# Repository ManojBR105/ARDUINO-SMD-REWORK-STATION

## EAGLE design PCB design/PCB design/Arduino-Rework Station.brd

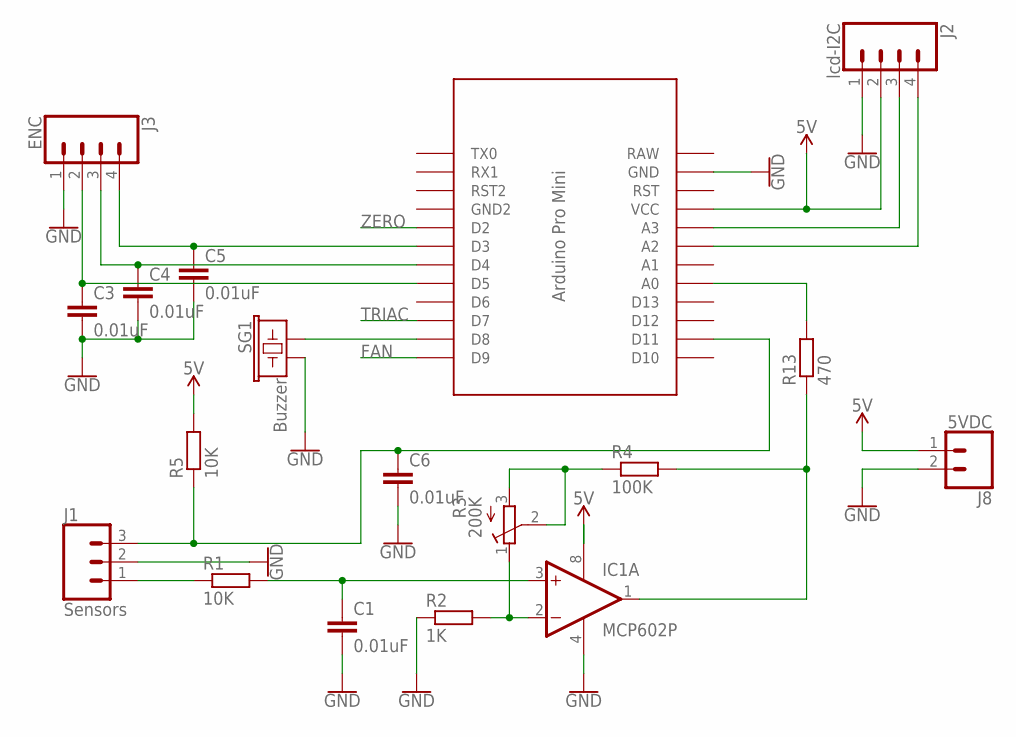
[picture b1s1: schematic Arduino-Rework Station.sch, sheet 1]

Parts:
C1, C3, C4, C5, C6: 0.01uF; C025-024X044
IC1: MCP602P; DIL08
J1: Sensors; MOLEX-1X3
J2: lcd-I2C; MOLEX-1X4
J3: ENC; MOLEX-1X4
J8: 5VDC; MOLEX-1X2
R1, R5: 10K; 0207/10
R2: 1K; 0207/10
R3: 200K; RTRIM3006P
R4: 100K; 0207/10
R13: 470; 0207/10
SG1: Buzzer; BUZZER-12MM
U$1: PRO-MINI

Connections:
5V: IC1.8 (V+), J2.2, J8.1, R5.2, U$1.VCC; also elsewhere on the board
FAN: U$1.D9; also elsewhere on the board
GND: C1.2, C3.2, C4.2, C5.2, C6.2, IC1.4 (V-), J1.2, J2.1, J3.1, J8.2, R2.1, SG1.- (2), U$1.GND; also elsewhere on the board
unnamed: C5.1, J3.4, U$1.D3
unnamed: C4.1, J3.3, U$1.D4
unnamed: C3.1, J3.2, U$1.D5
unnamed: J2.3, U$1.A3
unnamed: J2.4, U$1.A2
unnamed: J1.1, R1.1
unnamed: C1.1, IC1.3 (+IN), R1.2
unnamed: IC1.2 (-IN), R2.2, R3.1 (E)
unnamed: R3.2 (S), R3.3 (A), R4.1
unnamed: IC1.1 (OUT), R4.2, R13.1
unnamed: C6.1, J1.3, R5.1, U$1.D11
unnamed: SG1.+ (1), U$1.D8
unnamed: R13.2, U$1.A0
RAW: U$1.RAW
TRIAC: U$1.D7; also elsewhere on the board
ZERO: U$1.D2; also elsewhere on the board

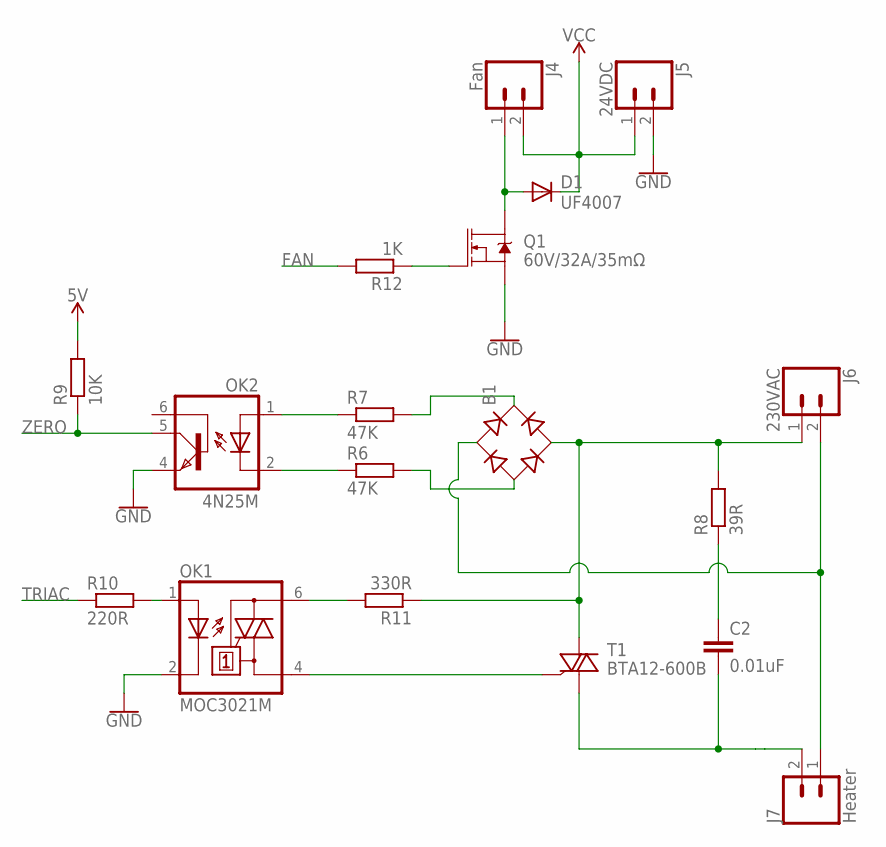
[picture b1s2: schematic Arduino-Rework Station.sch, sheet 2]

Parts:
B1: RB1A
C2: 0.01uF; C050-045X075
D1: UF4007; DO41-10
J4: Fan; MOLEX-1X2
J5: 24VDC; SCREWTERMINAL-5MM-2
J6: 230VAC; 1X02_XTRA_BIG
J7: Heater; 1X02_XTRA_BIG
OK1: MOC3021M; DIL06
OK2: 4N25M; DIL06
Q1: 60V/32A/35mΩ; TO220V
R6, R7: 47K; 0204/7
R8: 39R; 0617/22
R9: 10K; 0204/7
R10: 220R; 0204/7
R11: 330R; 0204/7
R12: 1K; 0204/7
T1: BTA12-600B; TO220BV

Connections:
5V: R9.2; also elsewhere on the board
FAN: R12.2; also elsewhere on the board
GND: J5.2, OK1.2 (C), OK2.4 (EMI), Q1.3 (S); also elsewhere on the board
unnamed: OK1.1 (A), R10.2
unnamed: OK2.1 (A), R7.1
unnamed: OK2.2 (C), R6.1
unnamed: B1.+, R7.2
unnamed: B1.-, R6.2
unnamed: B1.AC2, J6.1, R8.2, R11.1, T1.T2 (A2)
unnamed: C2.1, R8.1
unnamed: B1.AC1, J6.2, J7.1
unnamed: OK1.6 (A2), R11.2
unnamed: OK1.4 (A1), T1.G
unnamed: D1.A, J4.1, Q1.2 (D)
unnamed: C2.2, J7.2, T1.T1 (A1)
unnamed: Q1.1 (G), R12.1
TRIAC: R10.1; also elsewhere on the board
VCC: D1.C, J4.2, J5.1
ZERO: OK2.5 (COL), R9.1; also elsewhere on the board

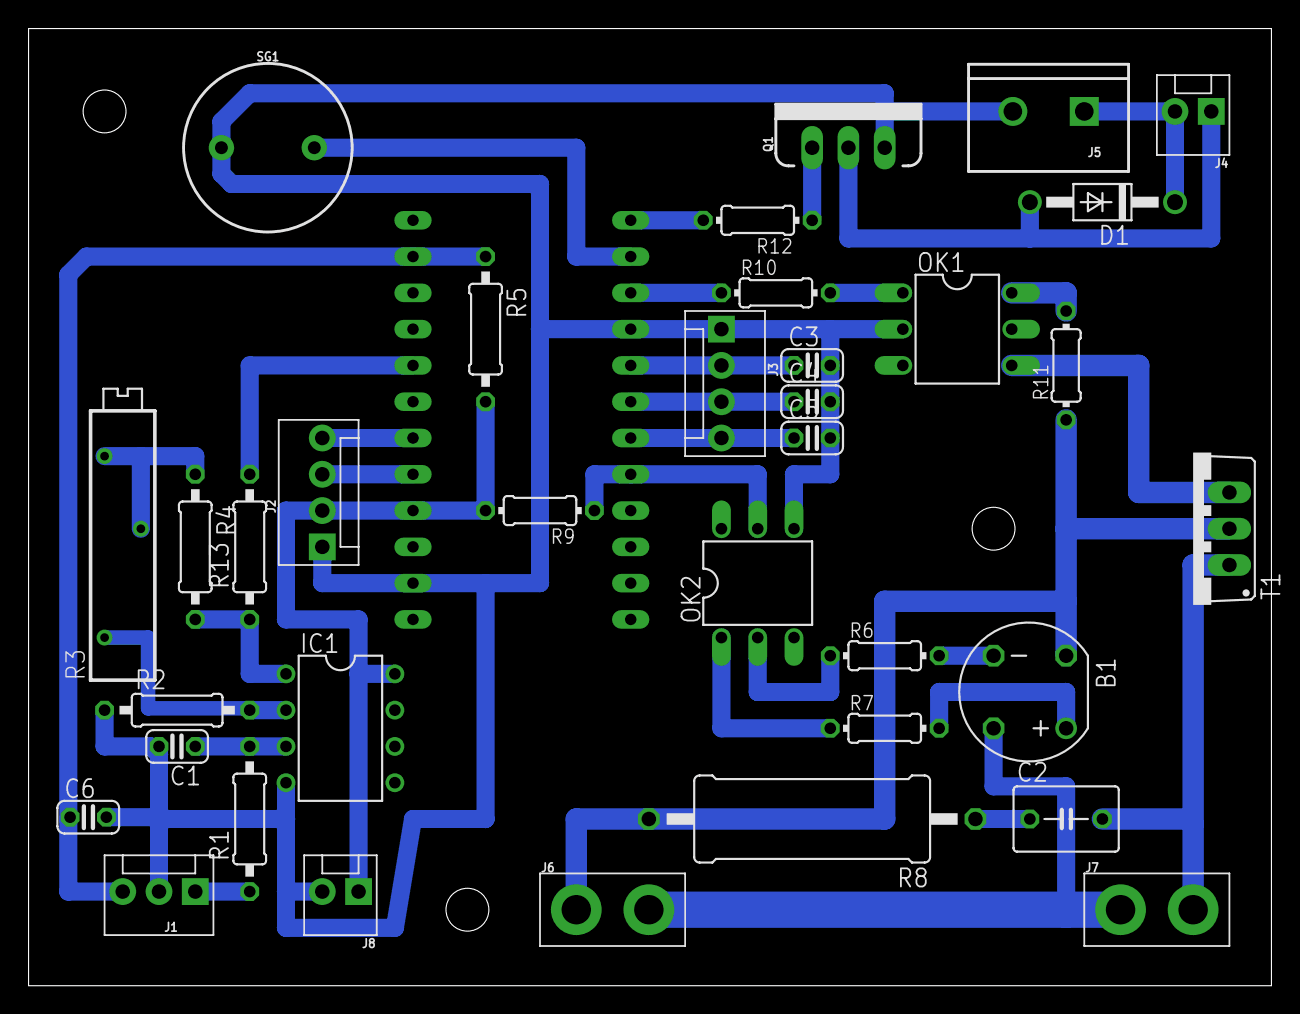
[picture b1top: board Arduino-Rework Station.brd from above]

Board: 2 copper layers, 87.0 x 67.0 mm, 36 parts (0 on the bottom side), 32 nets.

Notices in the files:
parts and their libraries:
SparkFun-Connectors: Licensing: Creative Commons ShareAlike 4.0 International - https://creativecommons.org/licenses/by-sa/4.0
